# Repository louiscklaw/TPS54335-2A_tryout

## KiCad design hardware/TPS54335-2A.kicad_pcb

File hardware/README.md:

# README

casual tryout for TI's TPS54335-2A to replace MP1584

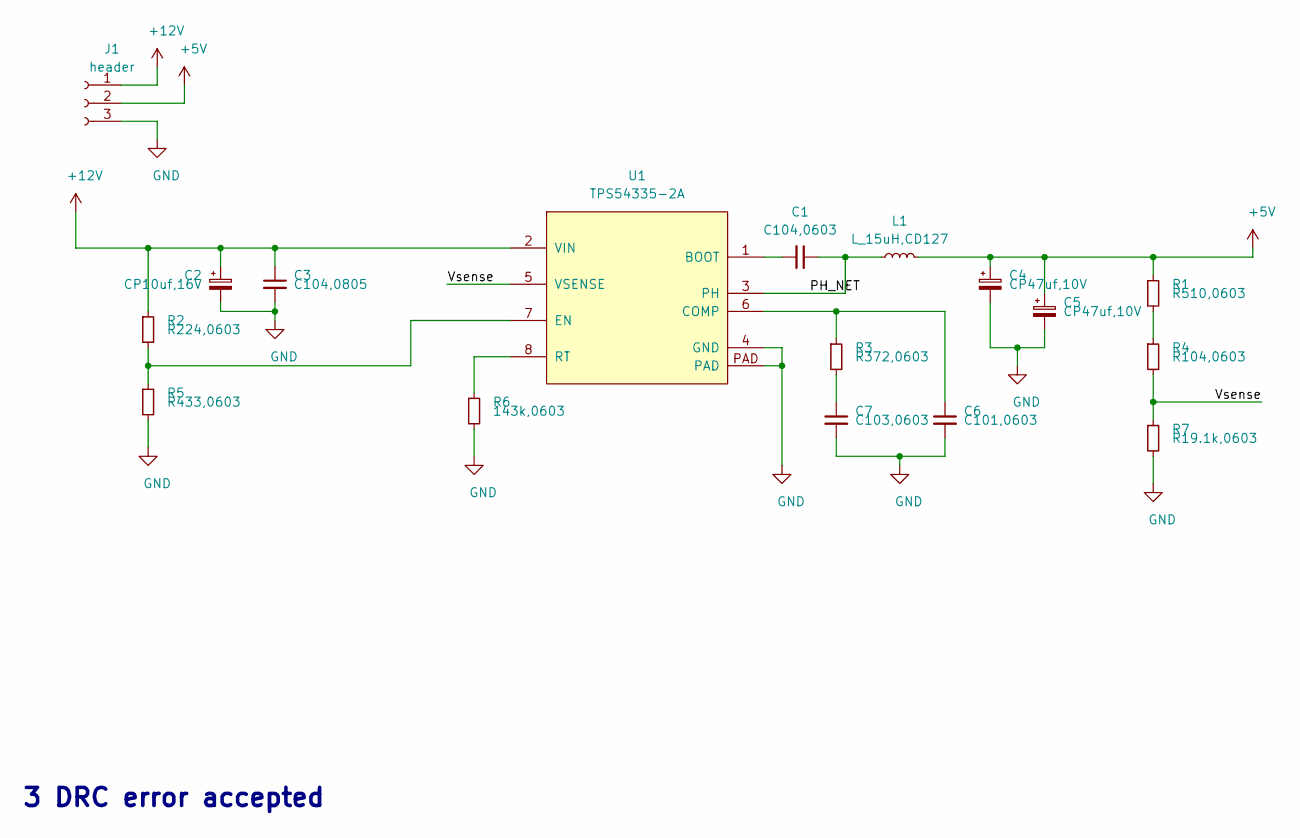
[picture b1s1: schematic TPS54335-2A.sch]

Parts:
C1: C104,0603; C_0603_1608Metric_Pad1.05x0.95mm_HandSolder
C2: CP10uf,16V; CP_Elec_4x5.3
C3: C104,0805; C_0805_2012Metric
C4, C5: CP47uf,10V; CP_Elec_4x5.3
C6: C101,0603; C_0603_1608Metric_Pad1.05x0.95mm_HandSolder
C7: C103,0603; C_0603_1608Metric_Pad1.05x0.95mm_HandSolder
J1: header; PinHeader_1x03_P1.27mm_Vertical
L1: L_15uH,CD127; L_CD127_shielded
R1: R510,0603; R_0603_1608Metric_Pad1.05x0.95mm_HandSolder
R2: R224,0603; R_0603_1608Metric_Pad1.05x0.95mm_HandSolder
R3: R372,0603; R_0603_1608Metric_Pad1.05x0.95mm_HandSolder
R4: R104,0603; R_0603_1608Metric_Pad1.05x0.95mm_HandSolder
R5: R433,0603; R_0603_1608Metric_Pad1.05x0.95mm_HandSolder
R6: 143k,0603; R_0603_1608Metric_Pad1.05x0.95mm_HandSolder
R7: R19.1k,0603; R_0603_1608Metric_Pad1.05x0.95mm_HandSolder
U1: TPS54335-2A; TPS54335ADDAR

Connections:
+5V: C4.1, C5.1, J1.2, L1.2, R1.1
+12V: C2.1, C3.1, J1.1, R2.1, U1.2 (VIN)
/PH_NET: C1.1, L1.1, U1.3 (PH)
/Vsense: R4.2, R7.1, U1.5 (VSENSE)
GND: C2.2, C3.2, C4.2, C5.2, C6.2, C7.2, J1.3, R5.2, R6.2, R7.2, U1.4 (GND), U1.PAD
unnamed: C1.2, U1.1 (BOOT)
unnamed: C6.1, R3.1, U1.6 (COMP)
unnamed: C7.1, R3.2
unnamed: R1.2, R4.1
unnamed: R2.2, R5.1, U1.7 (EN)
unnamed: R6.1, U1.8 (RT)

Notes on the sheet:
3 DRC error accepted

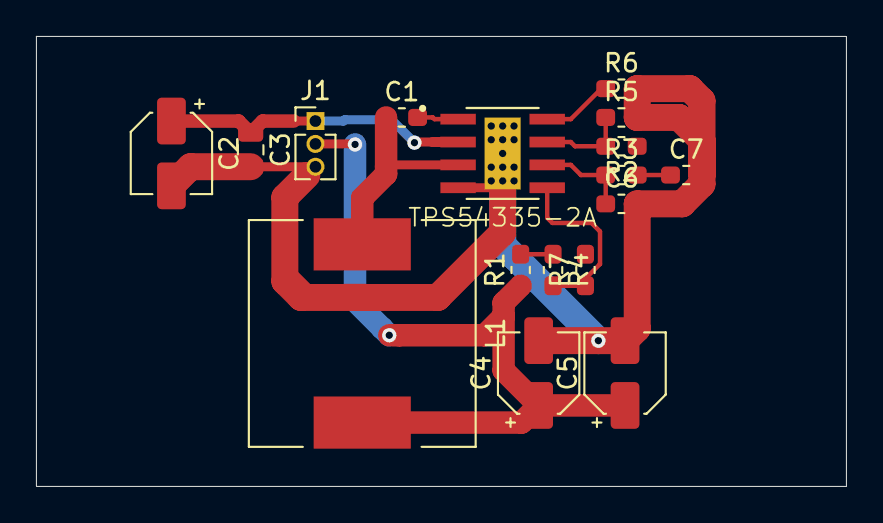
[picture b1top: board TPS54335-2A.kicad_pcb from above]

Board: 2 copper layers, 45.0 x 25.0 mm, 17 parts (0 on the bottom side), 11 nets.

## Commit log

2019-05-28 init commit,
2019-05-29 update for track width,
2019-05-29 update routing,
2020-05-07 ci: init travis build config,
2020-05-07 ci: init travis token,
